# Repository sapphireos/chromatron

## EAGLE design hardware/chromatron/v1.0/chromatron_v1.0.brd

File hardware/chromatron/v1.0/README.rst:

Chromatron Hardware v1.0
========================

`Chromatron Wifi Pixel Controller <http://chromatron.io>`_

License Information
-------------------

This work is licensed under the Creative Commons Attribution-ShareAlike 4.0 International License. To view a copy of this license, visit http://creativecommons.org/licenses/by-sa/4.0/ 

Note that if you intend to produce copies of this design for sale, the license does NOT include rights to use the Sapphire and Chromatron names and logos on the PCBs.

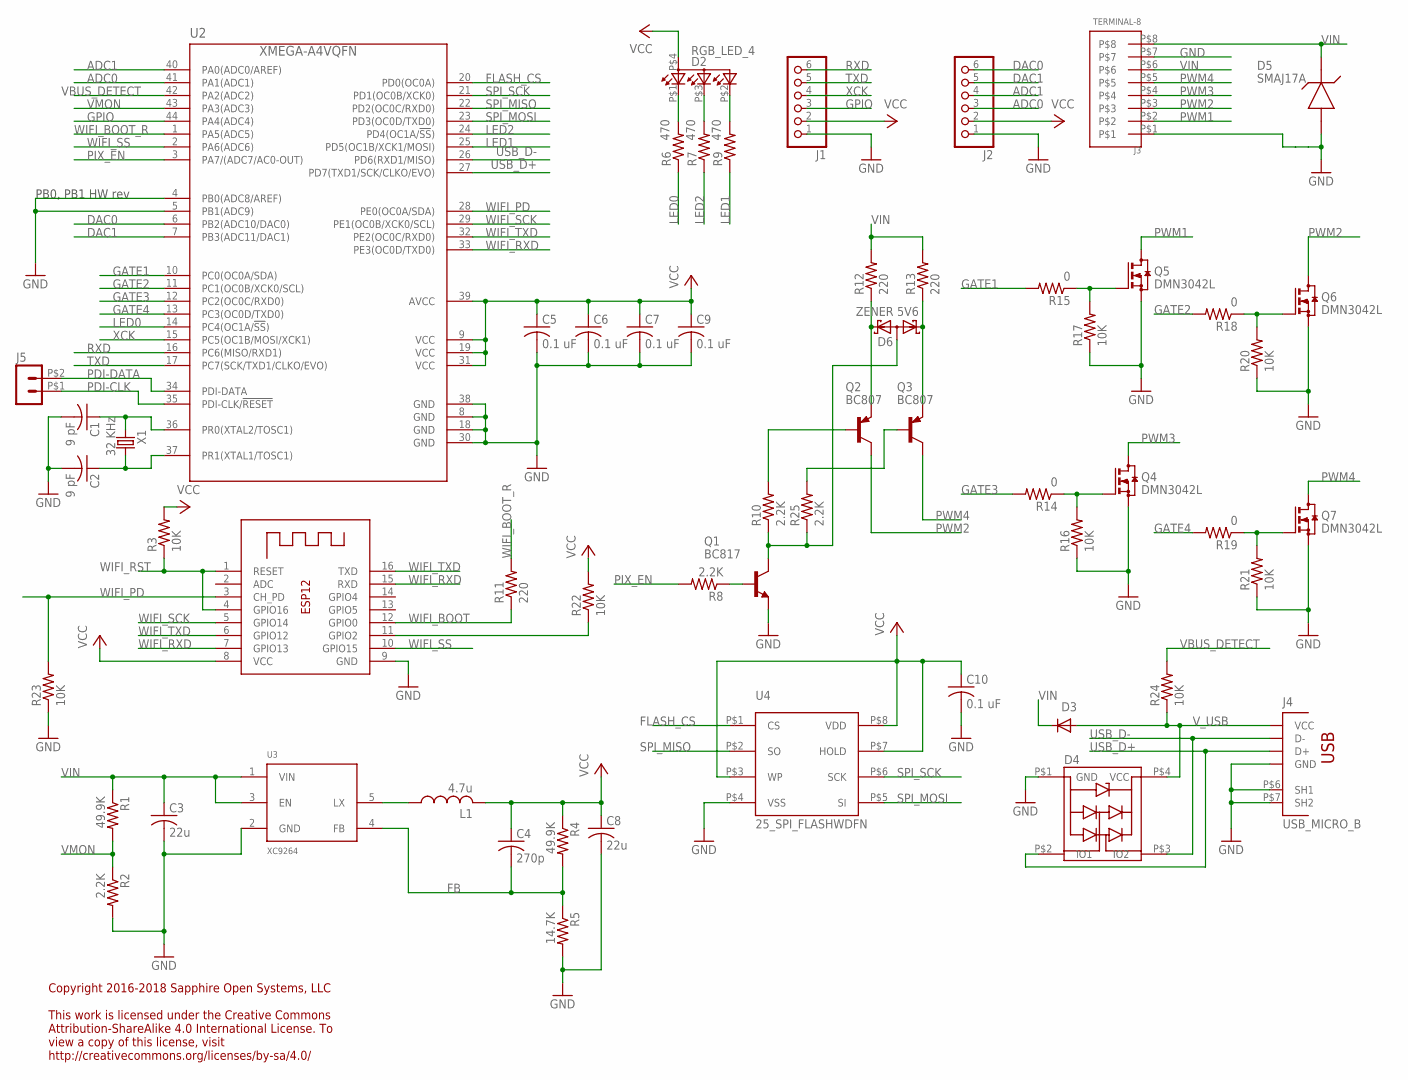
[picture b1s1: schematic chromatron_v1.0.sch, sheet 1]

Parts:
C1, C2: 9 pF; C0402
C3, C8: 22u; C1206
C4: 270p; C0402
C5, C6, C7, C9, C10: 0.1 uF; C0402
D2: RGB_LED_4; 0606-4
D3: 2A; SOD-123FL
D4: PTRTR5V0U2X; SOT-143B
D5: SMAJ17A; SMA
D6: ZENER 5V6; SOT23
J1, J2: PINHD-1X6; 1X06
J3: TERMINAL-8
J4: USB_MICRO_B; USB-MICRO-B
J5: PIN_HEADER_1X2
L1: 4.7u; L2012C
Q1: BC817; SOT23
Q2, Q3: BC807; SOT23
Q4, Q5, Q6, Q7: DMN3042L; SOT23
R1, R4: 49.9K; R0402
R2, R8, R10, R25: 2.2K; R0402
R3, R16, R17, R20, R21, R22, R23, R24: 10K; R0402
R5: 14.7K; R0402
R6, R7, R9: 470; R0402
R11, R12, R13: 220; R0402
R14, R15, R18, R19: 0; R0402
U1: ESP-12
U2: XMEGA-A4VQFN; QFN44
U3: XC9264; SOT-25
U4: 25_SPI_FLASHWDFN; WDFN-8
X1: 32 KHz; XTAL_3.2X1.5

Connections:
ADC0: J2.3, U2.41 (PA1(ADC1))
ADC1: J2.4, U2.40 (PA0(ADC0/AREF))
DAC0: J2.6, U2.6 (PB2(ADC10/DAC0))
DAC1: J2.5, U2.7 (PB3(ADC11/DAC1))
DEL: R22.1, U1.11 (GPIO2)
FB: C4.2, R4.2, R5.1, U3.4 (FB)
FLASH_CS: U2.20 (PD0(OC0A)), U4.P$1 (CS)
GATE1: R15.2, U2.10 (PC0(OC0A/SDA))
GATE2: R18.2, U2.11 (PC1(OC0B/XCK0/SCL))
GATE3: R14.2, U2.12 (PC2(OC0C/RXD0))
GATE4: R19.2, U2.13 (PC3(OC0D/TXD0))
GND: C1.2, C2.2, C3.2, C5.2, C6.2, C7.2, C8.2, C9.2, C10.2, D4.P$1 (GND), D5.P$2 (GND), J1.1, J2.1, J3.P$1, J3.P$7, J4.P$5 (GND), J4.P$6 (SH1), J4.P$7 (SH2), Q1.2 (E), Q4.2 (S), Q5.2 (S), Q6.2 (S), Q7.2 (S), R2.2, R5.2, R16.1, R17.1, R20.1, R21.1, R23.1, U1.9 (GND), U2.4 (PB0(ADC8/AREF)), U2.5 (PB1(ADC9)), U2.8 (GND), U2.18 (GND), U2.30 (GND), U2.38 (GND), U3.2 (GND), U4.P$4 (VSS)
GPIO: J1.3, U2.44 (PA4(ADC4))
LED0: R6.1, U2.14 (PC4(OC1A/!SS!))
LED1: R9.1, U2.25 (PD5(OC1B/XCK1/MOSI))
LED2: R7.1, U2.24 (PD4(OC1A/!SS!))
LX: L1.1, U3.5 (LX)
unnamed: D2.P$1 (CRED), R6.2
unnamed: D2.P$3 (CBLUE), R7.2
unnamed: C1.1, U2.36 (PR0(XTAL2/TOSC1)), X1.P$1 (1)
unnamed: C2.1, U2.37 (PR1(XTAL1/TOSC1)), X1.P$2 (2)
unnamed: D2.P$2 (CGREEN), R9.2
unnamed: D6.2 (K2), Q2.2 (E), R12.1
unnamed: Q3.1 (B), R25.2
unnamed: D6.1 (K1), Q3.2 (E), R13.1
unnamed: Q2.1 (B), R10.2
unnamed: D6.3 (AA), Q1.3 (C), R10.1, R25.1
unnamed: Q1.1 (B), R8.1
unnamed: Q7.1 (G), R19.1, R21.2
unnamed: Q6.1 (G), R18.1, R20.2
unnamed: Q5.1 (G), R15.1, R17.2
unnamed: Q4.1 (G), R14.1, R16.2
PDI-CLK: J5.P$1 (1), U2.35 (PDI-CLK/!RESET)
PDI-DATA: J5.P$2 (2), U2.34 (PDI-DATA)
PIX_EN: R8.2, U2.3 (PA7/(ADC7/AC0-OUT))
PWM1: J3.P$2, Q5.3 (D)
PWM2: J3.P$3, Q2.3 (C), Q6.3 (D)
PWM3: J3.P$4, Q4.3 (D)
PWM4: J3.P$5, Q3.3 (C), Q7.3 (D)
RXD: J1.6, U2.16 (PC6(MISO/RXD1))
SPI_MISO: U2.22 (PD2(OC0C/RXD0)), U4.P$2 (SO)
SPI_MOSI: U2.23 (PD3(OC0D/TXD0)), U4.P$5 (SI)
SPI_SCK: U2.21 (PD1(OC0B/XCK0)), U4.P$6 (SCK)
TXD: J1.5, U2.17 (PC7(SCK/TXD1/CLKO/EVO))
USB_D+: D4.P$2 (IO1), J4.P$3 (D+), U2.27 (PD7(TXD1/SCK/CLKO/EVO))
USB_D-: D4.P$3 (IO2), J4.P$2 (D-), U2.26 (PD6(RXD1/MISO))
VBUS_DETECT: R24.2, U2.42 (PA2(ADC2))
VCC: C4.1, C5.1, C6.1, C7.1, C8.1, C9.1, C10.1, D2.P$4 (A2), J1.2, J2.2, L1.2, R3.2, R4.1, R22.2, U1.8 (VCC), U2.9 (VCC), U2.19 (VCC), U2.31 (VCC), U2.39 (AVCC), U4.P$3 (WP), U4.P$7 (HOLD), U4.P$8 (VDD)
VIN: C3.1, D3.C, D5.P$1 (LINE), J3.P$6, J3.P$8, R1.1, R12.2, R13.2, U3.1 (VIN), U3.3 (EN)
VMON: R1.2, R2.1, U2.43 (PA3(ADC3))
V_USB: D3.A, D4.P$4 (VCC), J4.P$1 (VCC), R24.1
WIFI_BOOT: R11.1, U1.12 (GPIO0)
WIFI_BOOT_R: R11.2, U2.1 (PA5(ADC5))
WIFI_PD: R23.2, U1.3 (CH_PD), U2.28 (PE0(OC0A/SDA))
WIFI_RST: R3.1, U1.1 (RESET), U1.4 (GPIO16)
WIFI_RXD: U1.7 (GPIO13), U1.15 (RXD), U2.33 (PE3(OC0D/TXD0))
WIFI_SCK: U1.5 (GPIO14), U2.29 (PE1(OC0B/XCK0/SCL))
WIFI_SS: U1.10 (GPIO15), U2.2 (PA6(ADC6))
WIFI_TXD: U1.6 (GPIO12), U1.16 (TXD), U2.32 (PE2(OC0C/RXD0))
XCK: J1.4, U2.15 (PC5(OC1B/MOSI/XCK1))

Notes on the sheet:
PB0, PB1 HW rev
Copyright 2016-2018 Sapphire Open Systems, LLC This work is licensed under the Creative Commons Attribution-ShareAlike 4.0 International License. To view a copy of this license, visit http://creativecommons.org/licenses/by-sa/4.0/

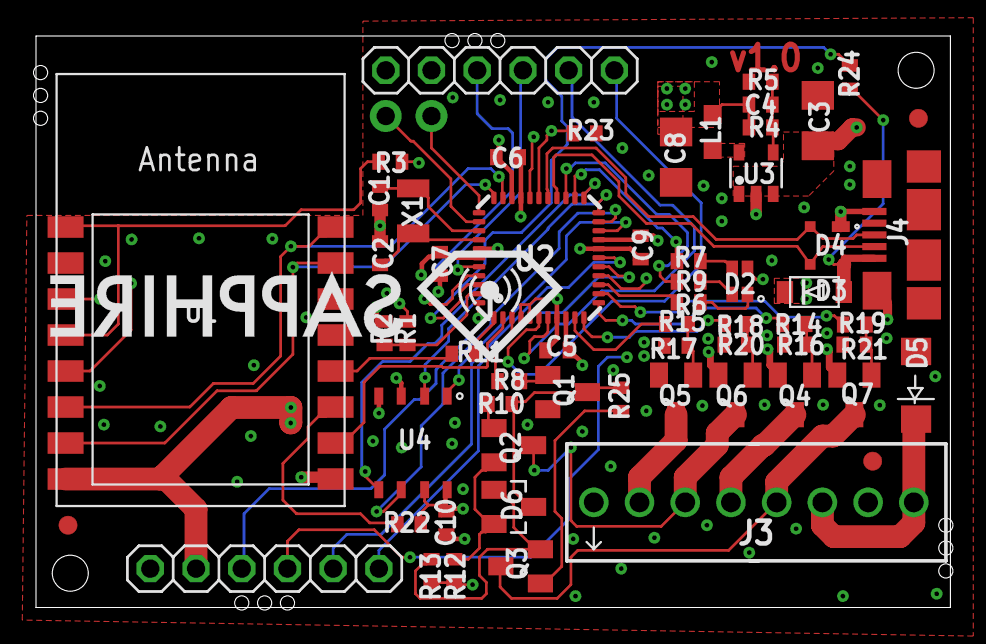
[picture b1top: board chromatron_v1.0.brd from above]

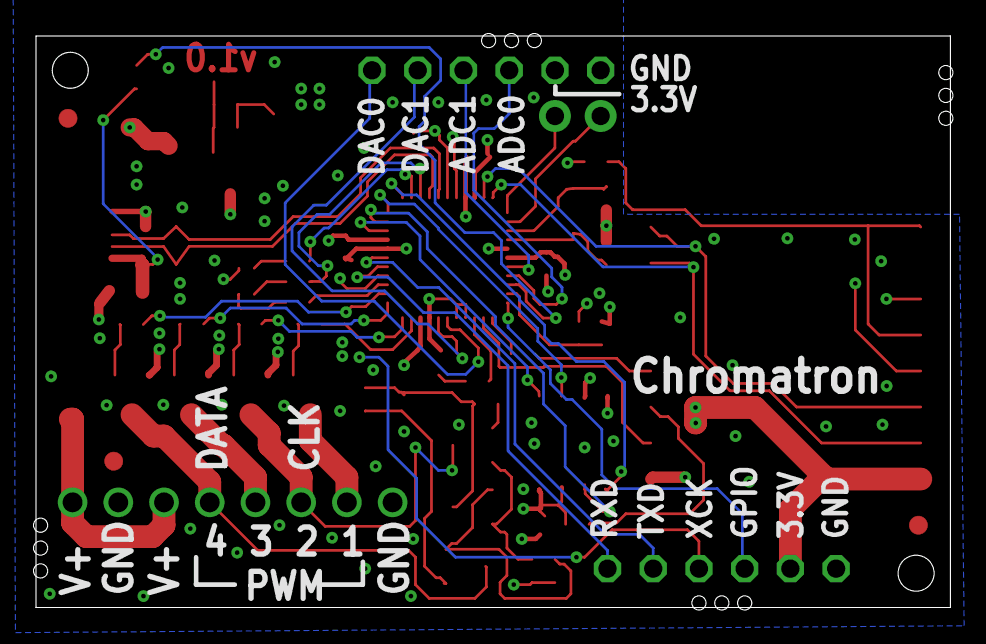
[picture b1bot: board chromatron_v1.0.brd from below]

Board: 4 copper layers, 50.8 x 31.8 mm, 68 parts (6 on the bottom side), 60 nets.

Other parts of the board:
DRILEGEND: DRILEGEND
U$1: SAPPHIRE_LOGO_0
U$2: SAPPHIRE_LOGO_NAME
U$3, U$4, U$5, U$6: MOUSE_BITE_3X
U$7, U$8, U$9: FID040

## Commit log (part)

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2025-06-22 error handling for readline
2025-06-22 Fix infinite loop in save scene
2025-06-22 scene clean up
2025-06-22 Add additional items to scenes
2025-07-20 Update button and pixel power FET controls to support 2025 board
2025-08-31 fix warning on header
2025-10-05 add accel driver init
2025-10-05 basic gyro support
2025-10-05 handle missing hw_type key
2025-10-05 Improve MPU9250 sample rate with bulk read
2025-10-31 add button support for 2025 board
2025-11-29 Add extended button support to ESP8266
2025-11-29 set new button option to persist
2025-12-07 Enable pixels on DC charge. Disable MQTT
2025-12-07 Pixels off in DC charge, some issue with pixel power control
2025-12-21 Add HX711 driver
2025-12-21 HX711 enable config
2025-12-21 Device DB, builds
2025-12-21 switching from multicast to broadcast
2025-12-22 device db clean up
2025-12-22 device db linkage with catbus announce
2025-12-22 device db vfile
2025-12-23 Only build hx711 on ESP32
2025-12-23 safe mode guard for device db
2025-12-23 catbus listen on announce sock
2025-12-23 join catbus announce multicast group
2025-12-23 fix port mapping bug
2025-12-23 turn off noisy log
2026-01-01 remove mqtt
2026-01-01 Remove msgflow
2026-01-01 Remove services
2026-01-02 work on ntp update
2026-01-06 source timestamp
2026-01-07 more ntp cleanup
2026-01-07 turn off controller sock
2026-01-07 bug fix
2026-01-07 set ntp timeout to 20 seconds for debug
2026-01-07 more ntp tweaks
2026-01-09 NTP updates
2026-01-09 AMG8833 driver
2026-01-09 HD44780 driver
2026-01-10 remove redundant pixel power init
2026-01-10 fix to pixel power init for charger2 boards
2026-01-11 fix build script for esp32 single
2026-01-11 Only run clock comparison on remote sources, not local master
2026-01-11 bug fix in battery power off
2026-01-15 turn off igmp and mcast
2026-01-21 work on timesync updates
2026-01-21 clean up
2026-01-21 work on timesync master selection
2026-01-21 work on link4
2026-01-21 sync debug
2026-01-21 debug
2026-01-22 update esp32 factory load script
2026-01-22 Add new flash mfg id
2026-01-22 dummy commit
2026-01-22 timesync debug
2026-01-24 timesync experiments
2026-01-24 tweaws
2026-01-24 timesync quality window
2026-01-24 Faster clock adjust on large delays
2026-01-24 traditional ping with RTT
2026-01-25 timesync clean up, using rtt algorithm. turn off cpu sleep in esp32 to improve latency
2026-01-25 time sync backoff
2026-01-25 master clock timeout
2026-01-25 increase timeout
2026-01-25 time sync tweaks, adjust max sleep intervals
2026-01-25 link creation machinery
2026-01-25 part of basic send machinery
2026-01-25 fix var shadowing
2026-01-25 basic remote receive
2026-01-25 enable fast block scan in safe mode
2026-01-25 bug fixes in receive path
2026-01-25 link timeout and delete
2026-01-25 data item timeout
2026-01-25 retransmit backoff
2026-01-26 work on recv
2026-01-26 start remote send
2026-01-29 VM4 scaffolding
2026-01-29 add fx4 array module from link
2026-01-30 more links to fx4
2026-01-30 Test vm load
2026-01-30 run VM
2026-01-30 gfx lib support for VM4
2026-01-30 VM4 thread
2026-01-30 VM tick loop
2026-01-30 VM coroutine stop handling
2026-01-30 tweaks
2026-01-30 basic on off control for vm4 testing
2026-01-30 vm timing
2026-01-30 cycle count
2026-01-31 Only start SNTP local clock if not already started
2026-02-01 fix assert in coproc reboot
2026-02-01 move coproc log message
2026-02-01 VM4 runner
2026-02-01 ntp fix
2026-02-01 VM runner fix
2026-02-01 link4 socket clean up
2026-02-01 clean up0
2026-02-01 Add gfx API to get fader step arrays
2026-02-01 remove debug
2026-02-07 pixelarray init
2026-02-20 pixel power bug fix from merge
2026-02-22 Fix I2C init
2026-02-22 I2C init in MCP23008 driver
2026-02-22 Rebuild ESP32 IDF, fix I2C timeout issues
2026-02-22 Add PCA9685 driver
2026-02-22 turn off trace
2026-02-22 backlight examples
2026-02-23 stub cron4
2026-02-23 LCD ui stub
2026-02-23 basic ui init
2026-02-23 LCD UI KV
2026-02-24 remove prometheus from python deps
2026-02-24 work on basic cron parser
2026-02-25 cron debug
2026-02-26 cron
2026-02-26 remove legacy gocd scripts
2026-02-27 cron updates
2026-03-01 reemove old controller and link protocols
2026-03-01 remove python link messages, unused and conflicts with catbus
2026-03-06 remove unused client code in catbus
2026-03-06 remove unused define
2026-03-06 Revert "remove unused define"
    This reverts commit 96a70f68faca478d3f8a04f1c0a1670e4611a48e.
2026-03-06 notes
2026-03-17 turn off unused catbus file hash lookup
2026-03-17 MPU9250 keys optional
2026-03-18 remove esp32 single core build script
2026-03-20 AMG data optional
2026-03-20 fix broken solar merge stuff - buttons, remove old drivers
2026-03-23 LCD UI enable control
2026-03-23 link4 fixes
2026-03-23 mem tracking for link4 db items
2026-03-23 link4 clean up
2026-03-23 link4 stats
2026-03-27 VM4 publish vars
2026-03-30 LCD support for 2 HD44780 chips
2026-03-30 Fix array wrap bug in catbus set/get for arrays
2026-03-31 Make announce chattier
2026-03-31 Catbus announce a bit more randomness
2026-04-04 Basic published var
2026-04-04 work on vm publish inbound
2026-04-04 fix 40x4 lcd
2026-04-04 lcd cgram support
2026-04-05 lcd tweaks
2026-04-05 stub superconductor
2026-04-05 work on superconductor
2026-04-06 Superconductor work
2026-04-11 FX4: update VM defines to VM4
2026-04-11 VM4: reset/run rework
2026-04-11 VM4: published var support for all var slots
2026-04-11 VM4: support all 4 VMs
2026-04-11 Link4: aggregations
2026-04-11 Fix legacy cron init to fix bad list
2026-04-11 VM4: program loader fixes
2026-04-11 VM4: debug log
2026-04-11 VM4: init update
2026-04-11 VM4: fix VM reset
2026-04-11 VM4: debug
2026-04-11 VM4: fix reset
2026-04-14 decimator
2026-04-14 starting FX4 sequencer integration
2026-04-14 cron notes
2026-04-14 vm4 stubs for sequencer
2026-04-15 start bespoke device server
2026-04-15 Make devicedb have its own protocol/server
2026-04-15 VM4 linkage to sequencer
2026-04-16 device db fixes
2026-04-17 device db add uptime and mode
2026-04-17 fix VM4 numbering
2026-04-17 cron4 integration
2026-04-17 bytecode function run tweaks
2026-04-17 cron fixes
2026-04-17 fix vm4 run when setting prog
2026-04-17 Stubs for VM sync, builds, definitely does not work lol
2026-04-18 device db stuff
2026-04-18 vm4 thread clean up
2026-04-18 drive VM4 timing from graphics clock
2026-04-18 vm timing fix
2026-04-19 Link4: partial support for recv
2026-04-19 Link4: remote timeout
2026-04-19 link4 work
2026-04-19 link4 debug
2026-04-20 link4 fix bad pointer calc
2026-04-20 link4 enable database timeout
2026-04-20 link4 fix database timeout processing
2026-04-20 link4 adjust timeouts
2026-04-20 work on vmsync4
2026-04-21 extend devicedb message with common useful info
2026-04-21 turn off timesync debug mode
2026-04-22 sequencer bug fix, add gfx apis
2026-04-22 turn off VM4 logs
2026-04-28 set announce sock to not bind to announce port
2026-04-28 Add sequence number to link data transfer
2026-04-28 log cleanup
2026-04-28 update link sequence number on receive
2026-04-28 fix link bugs
2026-04-28 link database rework
2026-04-28 link4 linkinfo
2026-04-28 link4 prune
2026-04-28 link4 console update
2026-04-28 allow stale sequences to time out
2026-04-28 Add extra link modes
2026-04-28 work on sync
2026-04-28 prune for sync
2026-04-28 add self database for sync
2026-04-28 move link timeout processing
2026-04-28 link fixes
2026-04-28 link sync mode database entry
2026-04-28 link debug
2026-04-29 sync4 work
2026-04-29 sync4 part of setup flow
2026-04-29 sync4 data transfer
2026-04-29 sync4 work on VM unfreeze logic
2026-04-30 sync4 debug
2026-04-30 fix vm id init
2026-04-30 Python tooling updates for VM4
2026-04-30 Python tooling fixes
2026-04-30 run VM4 tick separate from system clock
2026-04-30 turn off legacy sync
2026-04-30 sync data transfer
2026-04-30 add net time to sync messages
2026-04-30 sync work
2026-04-30 timing adjust
2026-04-30 sync work, use internal clocks instead of net
2026-05-01 sync insert/remove frames to catch up or slow down to server, maintains coroutine timing
2026-05-02 debug stats on sync
2026-05-03 header cleanup
2026-05-05 VM: make legacy FX3 VM optional with enable
2026-05-05 Seq: make sequencer current step persist
2026-05-06 Seq: manually persist sequencer step
2026-05-15 FS: fix wrong file count from legacy backup firmware image
2026-05-24 Add SapphireFirmware tooling
2026-05-24 Create separate fwinfo header
2026-05-27 Link4: header tweaks for inclusion in Command
2026-06-01 VM4: apply published var state from init
2026-06-01 VM4: type support for publish
2026-06-01 catbus fixed16 and float conversions for external tooling
2026-06-06 ESP32: uart driver enhancements
2026-06-27 fix SC decimator
2026-06-27 decimator range option

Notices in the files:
hardware/chromatron/v1.0/chromatron_v1.0.brd:
Copyright 2016-2017 Sapphire Open Systems, LLC
